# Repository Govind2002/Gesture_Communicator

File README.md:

# Assistive Communication Device

A gesture-based communication device designed to help people with sensory impairments communicate through predefined hand gestures. The system converts gestures into text displayed on an LCD and audio played through a speaker.

## Features
- Hand movement and orientation sensing using the MPU-6050 IMU
- Finger-bending detection using a flex sensor
- Gesture processing using Arduino Nano
- Wireless command transmission using HC-05 Bluetooth modules
- Text output on an LCD and audio output through a speaker

## Hardware
- Arduino Nano and Arduino Uno
- MPU-6050 IMU
- Flex sensor
- 2 × HC-05 Bluetooth modules
- LCD with I2C interface
- SD card reader and SD card
- PAM8403 audio amplifier and speaker

## Working
1. The glove sensors capture hand movement and finger bending.
2. The Arduino Nano identifies one of six predefined gestures and transmits its command over Bluetooth.
3. The Arduino Uno receives the command and displays the corresponding message on the LCD.
4. The associated prerecorded audio message is played through the speaker.

## Contributors
- Govind U
- S. Neha
- Sooraj A R

**Domain:** Embedded Systems, Sensors, Wireless Communication, Assistive Technology

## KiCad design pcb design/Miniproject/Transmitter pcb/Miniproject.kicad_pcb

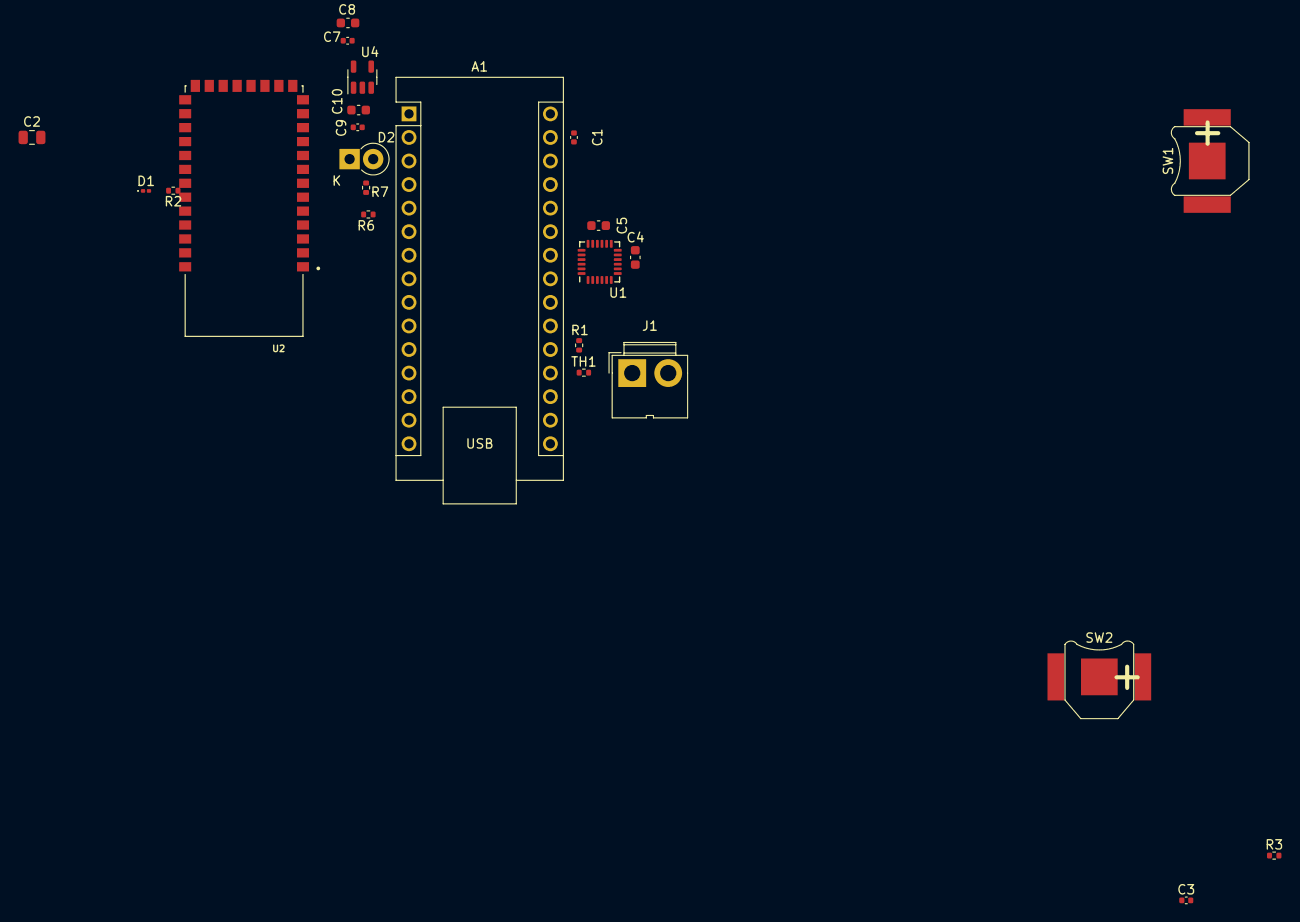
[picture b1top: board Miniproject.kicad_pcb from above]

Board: 2 copper layers, 24 parts (0 on the bottom side), 16 nets, no tracks yet.

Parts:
A1: Arduino_Nano_v3.x; Arduino_Nano
C1: 100n; C_0402_1005Metric
C2: 100u; C_0805_2012Metric
C3: 2.2nF; C_0402_1005Metric
C4, C5: 0.1uF; C_0603_1608Metric
C7, C9: 104; C_0402_1005Metric
C8, C10: 1u; C_0603_1608Metric
D1: RED LED; LED_0201_0603Metric
D2: 1.5KExxA; D_DO-41_SOD81_P2.54mm_Vertical_KathodeUp
J1: Conn_01x02_Socket; JWT_A3963_1x02_P3.96mm_Vertical
R1: 47K; R_0402_1005Metric
R2, R7: 2K; R_0402_1005Metric
R3: 10K; R_0402_1005Metric
R6: 1K; R_0402_1005Metric
SW1, SW2: SW_SPST; BatteryHolder_Keystone_2998_1x6.8mm
TH1: Thermistor; R_0402_1005Metric
U1: MPU-6050; InvenSense_QFN-24_4x4mm_P0.5mm
U2: HC-05; XCVR_HC-05
U4: XC6210B332MR; SOT-23-5

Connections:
/3.3 V: C7.1, C8.1, SW2.2 (B), U2.12 (3.3_VCC), U4.5 (VOUT)
/BRX: A1.5 (D2), R6.1
/BTX: A1.6 (D3), U2.1 (UART-TX)
/VCC: A1.27 (+5V), C5.2, D2.2 (A2), R1.1, U1.13 (VDD)
GND: A1.4 (GND), A1.29 (GND), C1.2, C2.2, C3.2, C4.2, C5.1, C7.2, C8.2, C9.2, C10.2, D1.1 (K), J1.1, R3.2, R7.2, TH1.2, U1.1 (CLKIN), U1.11 (FSYNC), U1.18 (GND), U2.13 (GND), U2.21 (GND), U2.22 (GND), U4.2 (GND)
unnamed: A1.19 (A0), R1.2, TH1.1
unnamed: A1.23 (A4), U1.24 (SDA)
unnamed: A1.24 (A5), U1.23 (SCL)
unnamed: A1.30 (VIN), C1.1, C2.1, SW1.1 (A)
unnamed: D1.2 (A), R2.2
unnamed: C9.1, C10.1, D2.1 (A1), U4.1 (VIN)
unnamed: J1.2, SW1.2 (B)
unnamed: R3.1, SW2.1 (A), U2.34 (PIO[11])
unnamed: C3.1, C4.1, U1.10 (REGOUT), U1.20 (CPOUT)
unnamed: R2.1, U2.31 (PIO[8])
unnamed: R6.2, R7.1, U2.2 (UART-RX)

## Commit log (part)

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2023-05-27 added file
2023-05-27 modified file
2023-05-29 Updated file
2023-05-29 Updated files
2023-07-30 added files
